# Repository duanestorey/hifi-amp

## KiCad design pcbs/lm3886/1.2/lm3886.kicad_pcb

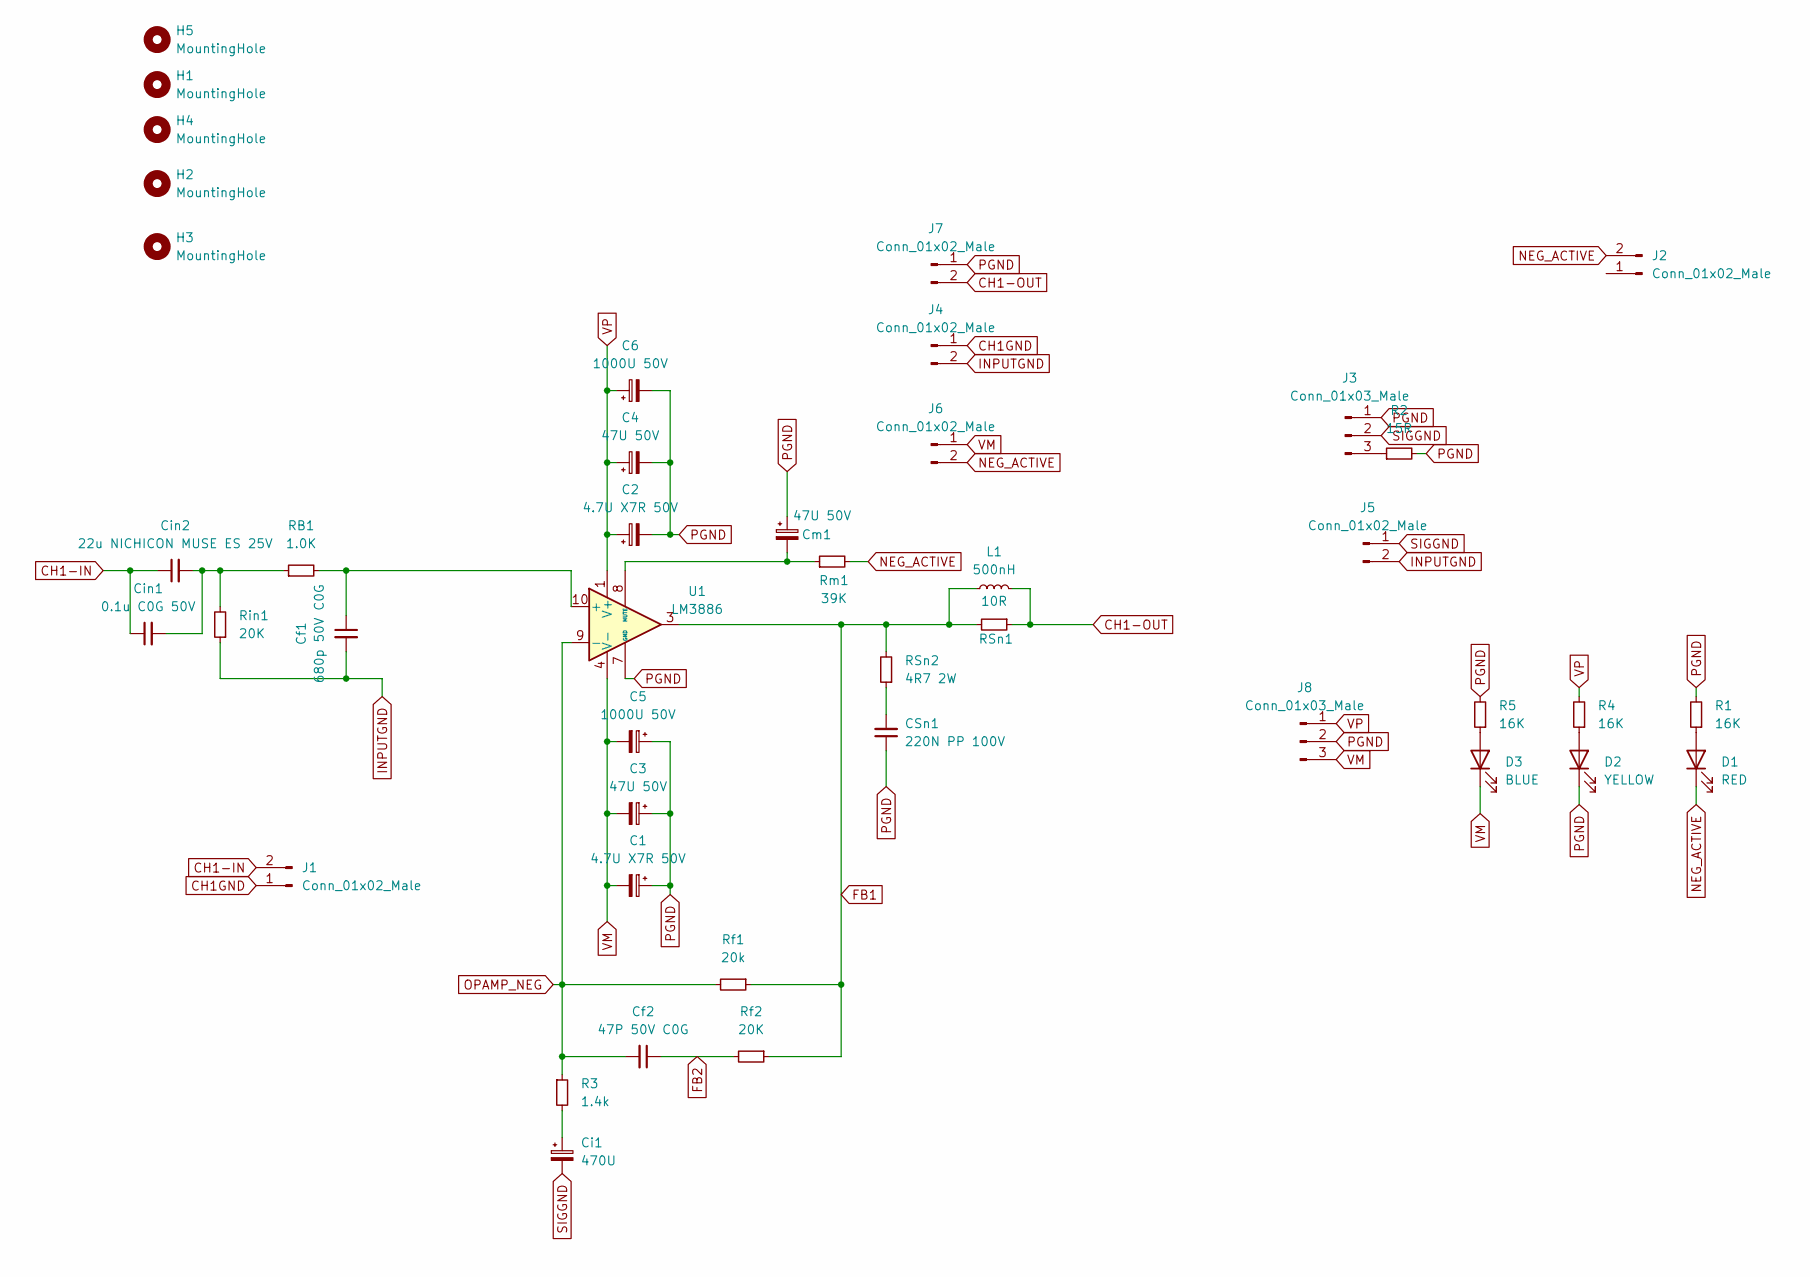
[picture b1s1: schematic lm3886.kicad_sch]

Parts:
C1, C2: 4.7U X7R 50V; C_1206_3216Metric_Pad1.33x1.80mm_HandSolder; Mouser 80-C1206X475J5RACTU
C3, C4: 47U 50V; CP_Radial_D6.3mm_P2.50mm
C5, C6: 1000U 50V; CP_Radial_D12.5mm_P5.00mm
CSn1: 220N PP 100V; C_Rect_L18.0mm_W7.0mm_P15.00mm_FKS3_FKP3; Mouser 505-MKP1D032204D00JB
Cf1: 680p 50V C0G; C_1206_3216Metric_Pad1.33x1.80mm_HandSolder; Mouser 603-CC126GRNPO9BN681
Cf2: 47P 50V C0G; C_1206_3216Metric_Pad1.33x1.80mm_HandSolder; Mouser 791-1206N470F500CT
Ci1: 470U; CP_Radial_D12.5mm_P5.00mm
Cin1: 0.1u C0G 50V; C_1206_3216Metric_Pad1.33x1.80mm_HandSolder; Mouser 81-GRT31C5C1H104FA2L
Cin2: 22u NICHICON MUSE ES 25V; C_Radial_D6.3mm_H5.0mm_P2.50mm
Cm1: 47U 50V; CP_Radial_D6.3mm_P2.50mm
D1: RED; LED_0805_2012Metric_Pad1.15x1.40mm_HandSolder
D2: YELLOW; LED_0805_2012Metric_Pad1.15x1.40mm_HandSolder
D3: BLUE; LED_0805_2012Metric_Pad1.15x1.40mm_HandSolder
H1, H2, H3, H4, H5: MountingHole; M3 Slot
J1, J2: Conn_01x02_Male; JST_PH_B2B-PH-K_1x02_P2.00mm_Vertical
J3: Conn_01x03_Male; PinHeader_1x03_P2.54mm_Vertical
J4, J5, J6: Conn_01x02_Male; PinHeader_1x02_P2.54mm_Vertical
J7: Conn_01x02_Male; JST_VH_B2P-VH_1x02_P3.96mm_Vertical
J8: Conn_01x03_Male; JST_VH_B3P-VH-B_1x03_P3.96mm_Vertical
L1: 500nH; 500nH Inductor Aliexpress Air Gap
R1, R4, R5: 16K; R_0603_1608Metric_Pad0.98x0.95mm_HandSolder
R2: 15R; R_1206_3216Metric_Pad1.30x1.75mm_HandSolder
R3: 1.4k; R_1206_3216Metric_Pad1.30x1.75mm_HandSolder; Mouser 603-RT1206FRE07750RL
RB1: 1.0K; R_1206_3216Metric_Pad1.30x1.75mm_HandSolder; Mouser 603-RT1206FRE131KL
RSn1: 10R; R_4020_10251Metric_Pad1.65x5.30mm_HandSolder; Mouser 279-355010RJT
RSn2: 4R7 2W; R_2512_6332Metric_Pad1.40x3.35mm_HandSolder; Mouser 603-RC2512JK-7W4R7
Rf1: 20k; R_1206_3216Metric_Pad1.30x1.75mm_HandSolder; Mouser 603-RT1206FRD0720KL
Rf2: 20K; R_1206_3216Metric_Pad1.30x1.75mm_HandSolder; Mouser 603-RT1206FRD0720KL
Rin1: 20K; R_1206_3216Metric_Pad1.30x1.75mm_HandSolder; Mouser 603-RT1206FRD0720KL
Rm1: 39K; R_1206_3216Metric_Pad1.30x1.75mm_HandSolder; Mouser 603-RC1206JR-0739KL
U1: LM3886; TO-220-11_P3.4x5.08mm_StaggerOdd_Lead4.85mm_Vertical

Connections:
CH1-IN: Cin1.1, Cin2.1, J1.2
CH1-OUT: J7.2, L1.2, RSn1.1
CH1GND: J1.1, J4.1
FB1: L1.1, RSn1.2, RSn2.2, Rf1.1, Rf2.1, U1.3
FB2: Cf2.1, Rf2.2
INPUTGND: Cf1.2, J4.2, J5.2, Rin1.1
NEG_ACTIVE: D1.1 (K), J2.2, J6.2, Rm1.2
unnamed: CSn1.2, RSn2.1
unnamed: Ci1.1, R3.2
unnamed: Cin1.2, Cin2.2, RB1.1, Rin1.2
unnamed: D1.2 (A), R1.1
unnamed: D2.2 (A), R4.1
unnamed: D3.2 (A), R5.1
unnamed: J3.3, R2.1
unnamed: Cf1.1, RB1.2, U1.10 (+)
unnamed: Cm1.2, Rm1.1, U1.8 (MUTE)
OPAMP_NEG: Cf2.2, R3.1, Rf1.2, U1.9 (-)
PGND: C1.1, C2.2, C3.1, C4.2, C5.1, C6.2, CSn1.1, Cm1.1, D2.1 (K), J3.1, J7.1, J8.2, R1.2, R2.2, R5.2, U1.7 (GND)
SIGGND: Ci1.2, J3.2, J5.1
VM: C1.2, C3.2, C5.2, D3.1 (K), J6.1, J8.3, U1.4 (V-)
VP: C2.1, C4.1, C6.1, J8.1, R4.2, U1.1 (V+), U1.5 (V+)

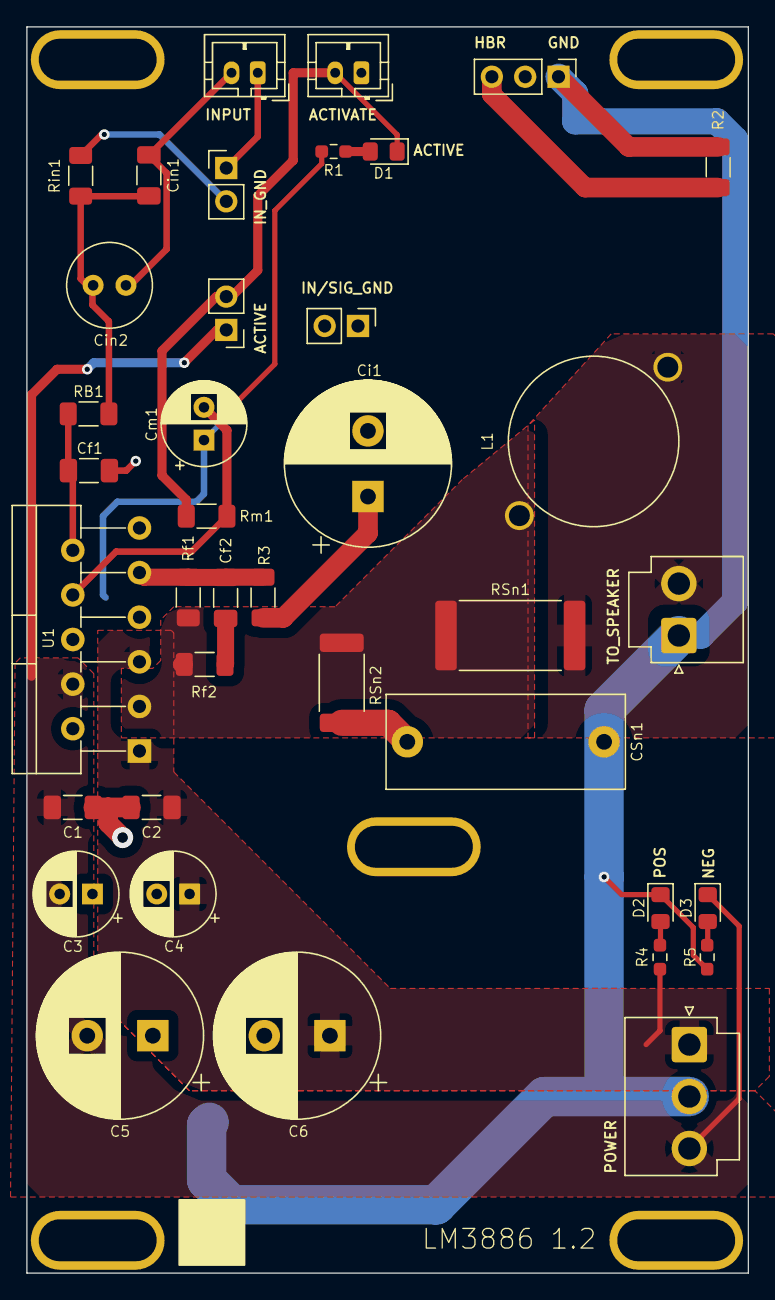
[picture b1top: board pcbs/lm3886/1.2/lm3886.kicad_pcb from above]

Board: 2 copper layers, 55.0 x 95.0 mm, 43 parts (0 on the bottom side), 21 nets.

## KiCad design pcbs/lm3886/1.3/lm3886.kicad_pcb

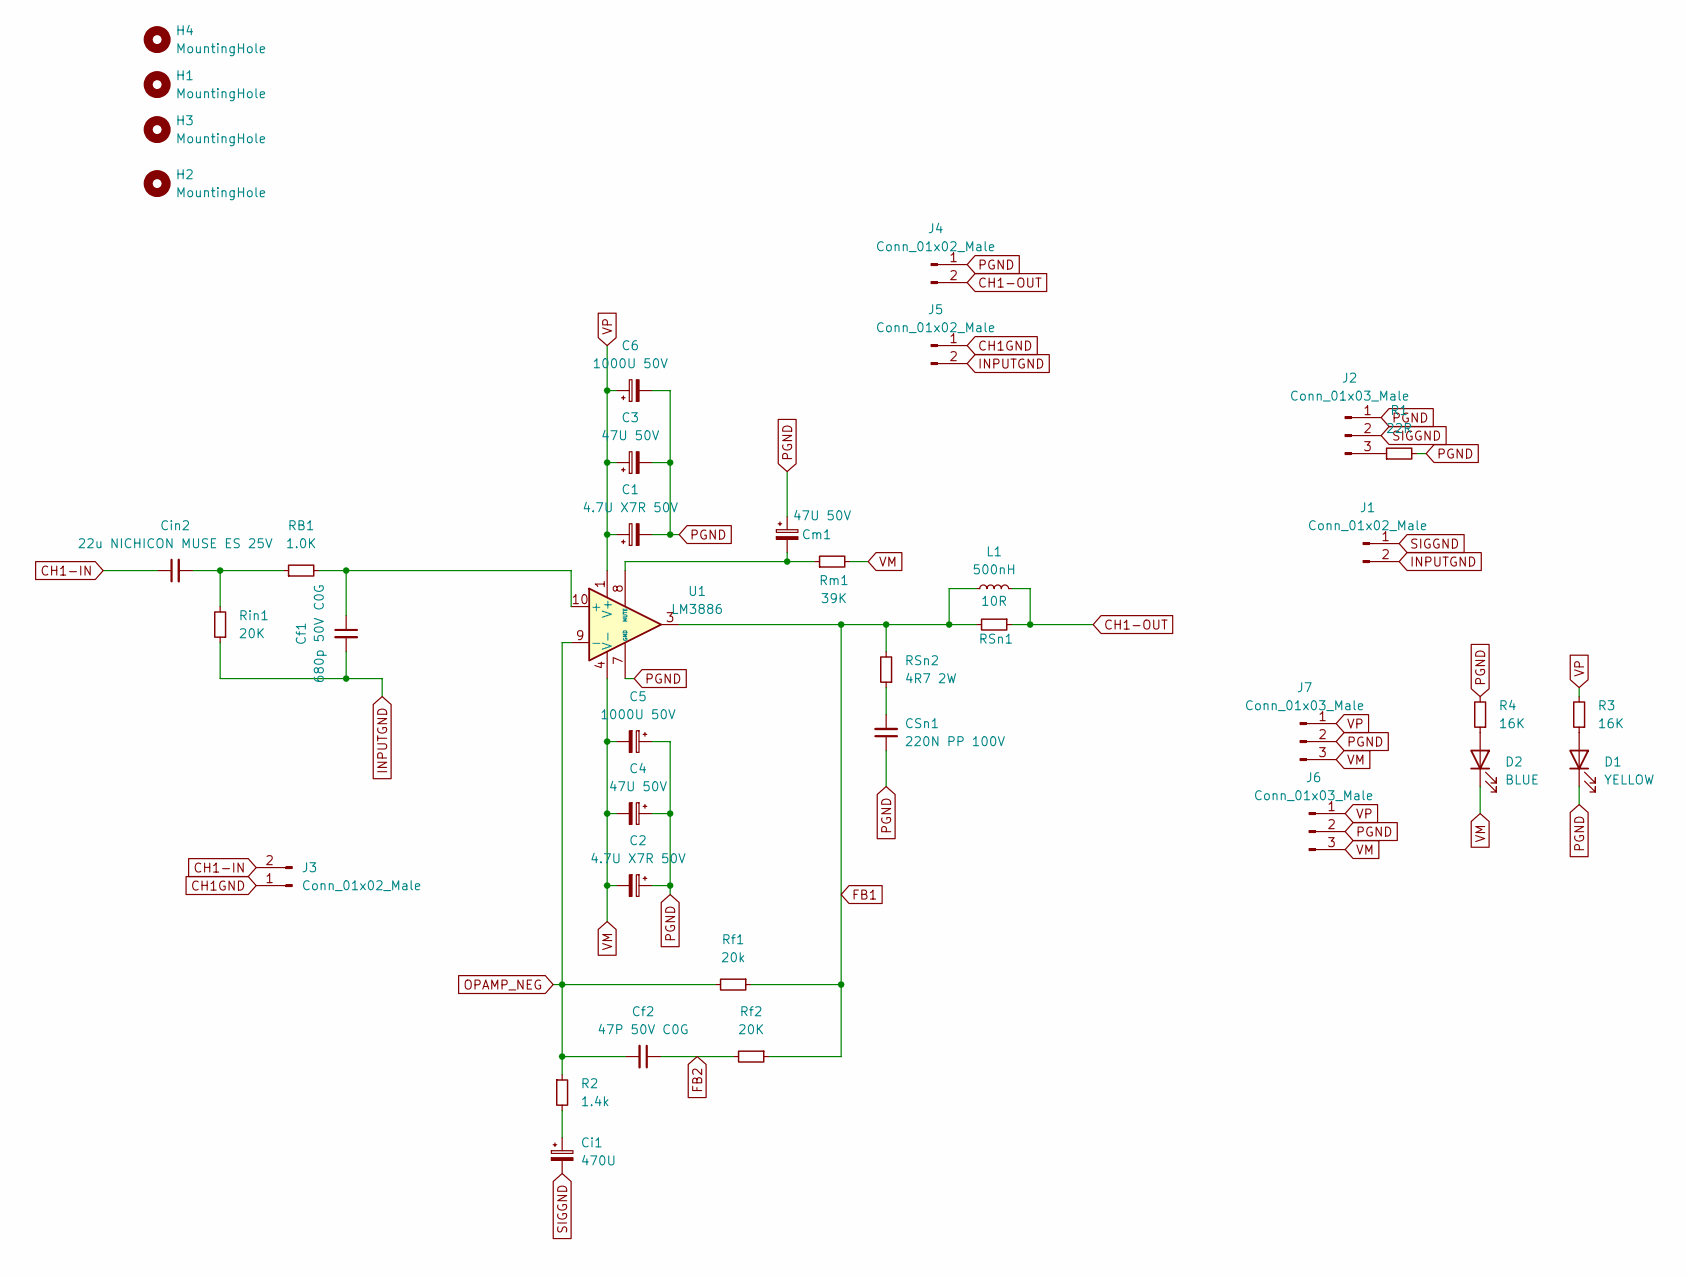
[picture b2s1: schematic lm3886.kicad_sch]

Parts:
C1, C2: 4.7U X7R 50V; C_1206_3216Metric_Pad1.33x1.80mm_HandSolder; Mouser 80-C1206X475J5RACTU
C3, C4: 47U 50V; CP_Radial_D6.3mm_P2.50mm
C5, C6: 1000U 50V; CP_Radial_D12.5mm_P5.00mm
CSn1: 220N PP 100V; C_Rect_L18.0mm_W7.0mm_P15.00mm_FKS3_FKP3; Mouser 505-MKP1D032204D00JB
Cf1: 680p 50V C0G; C_1206_3216Metric_Pad1.33x1.80mm_HandSolder; Mouser 603-CC126GRNPO9BN681
Cf2: 47P 50V C0G; C_1206_3216Metric_Pad1.33x1.80mm_HandSolder; Mouser 791-1206N470F500CT
Ci1: 470U; CP_Radial_D12.5mm_P5.00mm
Cin2: 22u NICHICON MUSE ES 25V; C_Radial_D6.3mm_H5.0mm_P2.50mm
Cm1: 47U 50V; CP_Radial_D6.3mm_P2.50mm
D1: YELLOW; LED_0805_2012Metric_Pad1.15x1.40mm_HandSolder
D2: BLUE; LED_0805_2012Metric_Pad1.15x1.40mm_HandSolder
H1, H2, H3, H4: MountingHole; MountingHole_3.2mm_M3_DIN965_Pad_TopOnly
J1, J5: Conn_01x02_Male; PinHeader_1x02_P2.54mm_Vertical
J2: Conn_01x03_Male; PinHeader_1x03_P2.54mm_Vertical
J3: Conn_01x02_Male; JST_PH_B2B-PH-K_1x02_P2.00mm_Vertical
J4: Conn_01x02_Male; JST_VH_B2P-VH_1x02_P3.96mm_Vertical
J6, J7: Conn_01x03_Male; JST_VH_B3P-VH-B_1x03_P3.96mm_Vertical
L1: 500nH; 500nH Inductor Aliexpress Air Gap
R1: 22R; R_1206_3216Metric_Pad1.30x1.75mm_HandSolder
R2: 1.4k; R_1206_3216Metric_Pad1.30x1.75mm_HandSolder; Mouser 603-RT1206FRE07750RL
R3, R4: 16K; R_0603_1608Metric_Pad0.98x0.95mm_HandSolder
RB1: 1.0K; R_1206_3216Metric_Pad1.30x1.75mm_HandSolder; Mouser 603-RT1206FRE131KL
RSn1: 10R; R_4020_10251Metric_Pad1.65x5.30mm_HandSolder; Mouser 279-355010RJT
RSn2: 4R7 2W; R_2512_6332Metric_Pad1.40x3.35mm_HandSolder; Mouser 603-RC2512JK-7W4R7
Rf1: 20k; R_1206_3216Metric_Pad1.30x1.75mm_HandSolder; Mouser 603-RT1206FRD0720KL
Rf2: 20K; R_1206_3216Metric_Pad1.30x1.75mm_HandSolder; Mouser 603-RT1206FRD0720KL
Rin1: 20K; R_1206_3216Metric_Pad1.30x1.75mm_HandSolder; Mouser 603-RT1206FRD0720KL
Rm1: 39K; R_1206_3216Metric_Pad1.30x1.75mm_HandSolder; Mouser 603-RC1206JR-0739KL
U1: LM3886; TO-220-11_P3.4x5.08mm_StaggerOdd_Lead4.85mm_Vertical

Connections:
CH1-IN: Cin2.1, J3.2; also elsewhere on the board
CH1-OUT: J4.2, L1.2, RSn1.1
CH1GND: J3.1, J5.1
FB1: L1.1, RSn1.2, RSn2.2, Rf1.1, Rf2.1, U1.3
FB2: Cf2.1, Rf2.2
INPUTGND: Cf1.2, J1.2, J5.2, Rin1.1
unnamed: CSn1.2, RSn2.1
unnamed: Ci1.1, R2.2
unnamed 8: Cin2.2, RB1.1, Rin1.2; also elsewhere on the board
unnamed: D1.2 (A), R3.1
unnamed: D2.2 (A), R4.1
unnamed: J2.3, R1.1
unnamed: Cf1.1, RB1.2, U1.10 (+)
unnamed: Cm1.2, Rm1.1, U1.8 (MUTE)
OPAMP_NEG: Cf2.2, R2.1, Rf1.2, U1.9 (-)
PGND: C1.2, C2.1, C3.2, C4.1, C5.1, C6.2, CSn1.1, Cm1.1, D1.1 (K), J2.1, J4.1, J6.2, J7.2, R1.2, R4.2, U1.7 (GND)
SIGGND: Ci1.2, J1.1, J2.2
VM: C2.2, C4.2, C5.2, D2.1 (K), J6.3, J7.3, Rm1.2, U1.4 (V-)
VP: C1.1, C3.1, C6.1, J6.1, J7.1, R3.2, U1.1 (V+), U1.5 (V+)

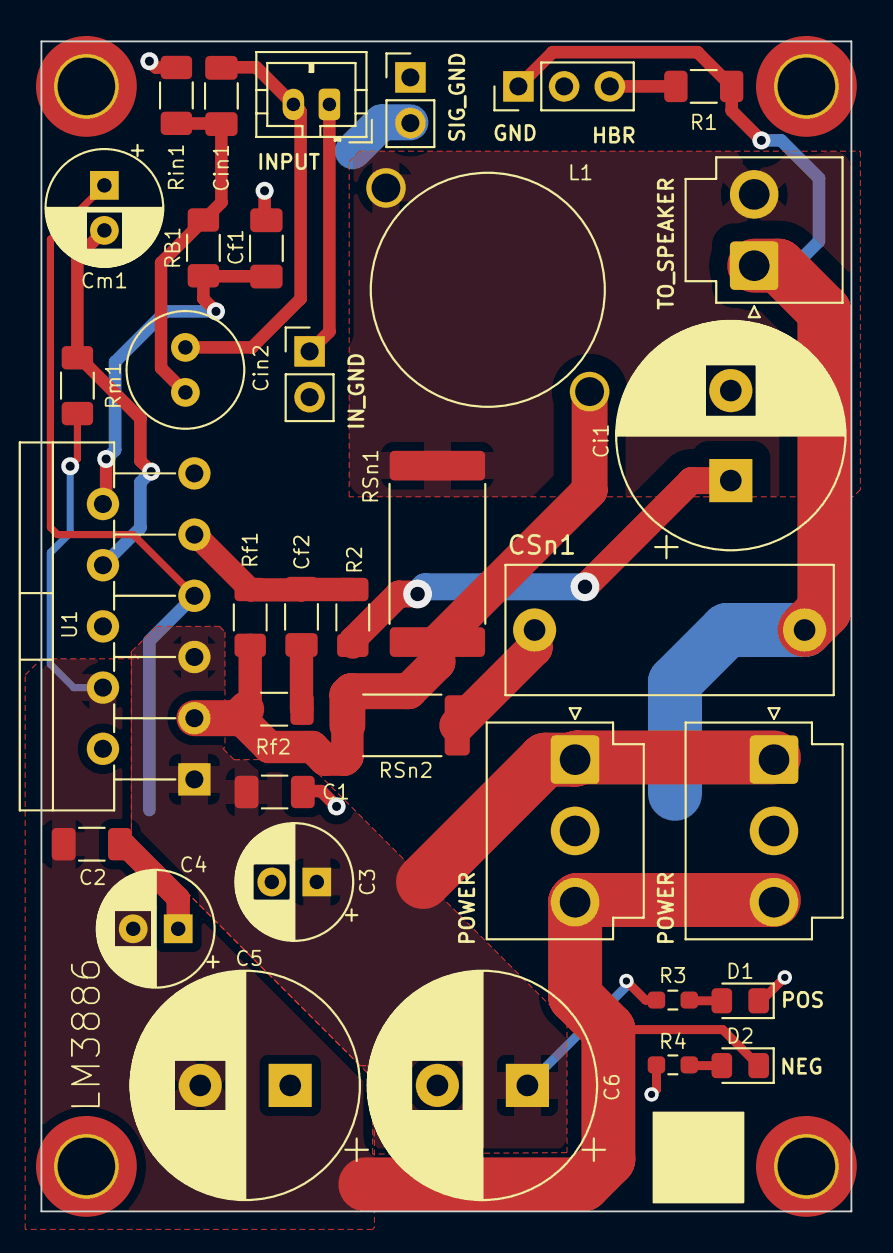
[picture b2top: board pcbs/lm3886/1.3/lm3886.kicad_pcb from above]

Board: 2 copper layers, 45.0 x 65.0 mm, 39 parts (0 on the bottom side), 19 nets.

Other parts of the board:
Cin1: 0.1u C0G 50V; C_1206_3216Metric_Pad1.33x1.80mm_HandSolder

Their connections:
CH1-IN: Cin1.1; also elsewhere on the board
unnamed 8: Cin1.2; also elsewhere on the board

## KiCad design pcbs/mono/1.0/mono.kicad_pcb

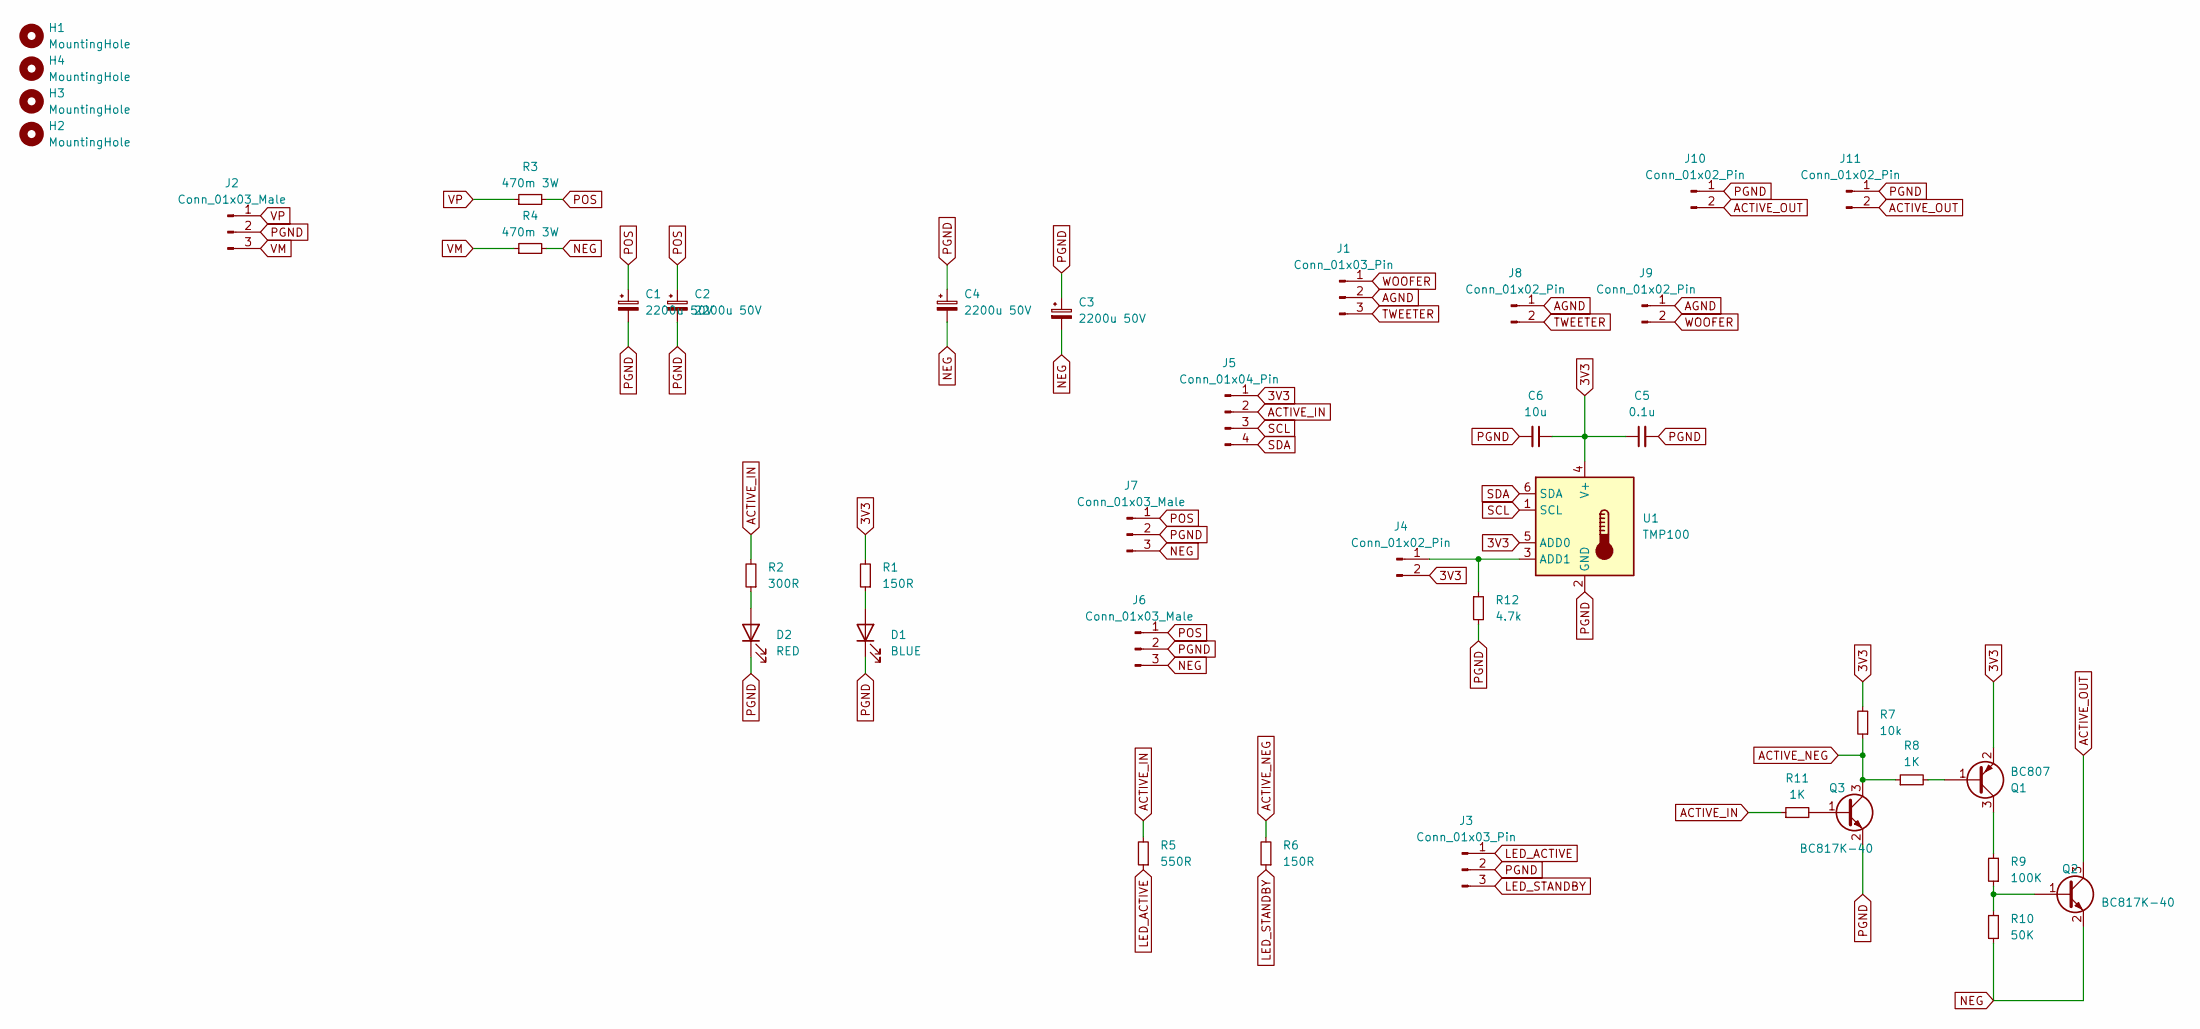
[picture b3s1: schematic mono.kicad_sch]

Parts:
C1, C2, C3, C4: 2200u 50V; CP_Radial_D16.0mm_P7.50mm; Mouser 80-ESH228M050AM3AA
C5: 0.1u; C_0805_2012Metric_Pad1.18x1.45mm_HandSolder
C6: 10u; C_1206_3216Metric_Pad1.33x1.80mm_HandSolder
D1: BLUE; LED_0603_1608Metric_Pad1.05x0.95mm_HandSolder
D2: RED; LED_0603_1608Metric_Pad1.05x0.95mm_HandSolder
H1, H2, H3, H4: MountingHole; MountingHole_3.2mm_M3_DIN965_Pad_TopOnly
J1, J3: Conn_01x03_Pin; JST_PH_B3B-PH-K_1x03_P2.00mm_Vertical
J2, J6, J7: Conn_01x03_Male; JST_VH_B3P-VH-B_1x03_P3.96mm_Vertical
J4: Conn_01x02_Pin; PinHeader_1x02_P2.54mm_Vertical
J5: Conn_01x04_Pin; JST_PH_B4B-PH-K_1x04_P2.00mm_Vertical
J8, J9, J10, J11: Conn_01x02_Pin; JST_PH_B2B-PH-K_1x02_P2.00mm_Vertical
Q1: BC807; TSOT-23; Mouser 637-BC807-16
Q2, Q3: BC817K-40; TSOT-23; Mouser 637-BC817K-40
R1, R6: 150R; R_0603_1608Metric_Pad0.98x0.95mm_HandSolder
R2: 300R; R_0603_1608Metric_Pad0.98x0.95mm_HandSolder
R3, R4: 470m 3W; R_1218_3246Metric_Pad1.22x4.75mm_HandSolder; Mouser RLW73PA3FR47TDF
R5: 550R; R_0603_1608Metric_Pad0.98x0.95mm_HandSolder
R7: 10k; R_0603_1608Metric_Pad0.98x0.95mm_HandSolder
R8, R11: 1K; R_0603_1608Metric_Pad0.98x0.95mm_HandSolder
R9: 100K; R_0603_1608Metric_Pad0.98x0.95mm_HandSolder
R10: 50K; R_0603_1608Metric_Pad0.98x0.95mm_HandSolder
R12: 4.7k; R_0603_1608Metric_Pad0.98x0.95mm_HandSolder
U1: TMP100; SOT-23-6

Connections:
3V3: C5.1, C6.1, J4.2, J5.1, Q1.2 (E), R1.2, R7.2, U1.4 (V+), U1.5 (ADD0)
ACTIVE_IN: J5.2, R2.2, R5.2, R11.1
ACTIVE_NEG: Q3.3 (C), R6.2, R7.1, R8.1
ACTIVE_OUT: J10.2, J11.2, Q2.3 (C)
AGND: J1.2, J8.1, J9.1
LED_ACTIVE: J3.1, R5.1
LED_STANDBY: J3.3, R6.1
NEG: C3.2, C4.2, J6.3, J7.3, Q2.2 (E), R4.2, R10.1
unnamed: D1.2 (A), R1.1
unnamed: D2.2 (A), R2.1
unnamed: J4.1, R12.1, U1.3 (ADD1)
unnamed: Q1.1 (B), R8.2
unnamed: Q1.3 (C), R9.2
unnamed: Q2.1 (B), R9.1, R10.2
unnamed: Q3.1 (B), R11.2
PGND: C1.2, C2.2, C3.1, C4.1, C5.2, C6.2, D1.1 (K), D2.1 (K), J2.2, J3.2, J6.2, J7.2, J10.1, J11.1, Q3.2 (E), R12.2, U1.2 (GND)
POS: C1.1, C2.1, J6.1, J7.1, R3.2
SCL: J5.3, U1.1 (SCL)
SDA: J5.4, U1.6 (SDA)
TWEETER: J1.3, J8.2
VM: J2.3, R4.1
VP: J2.1, R3.1
WOOFER: J1.1, J9.2

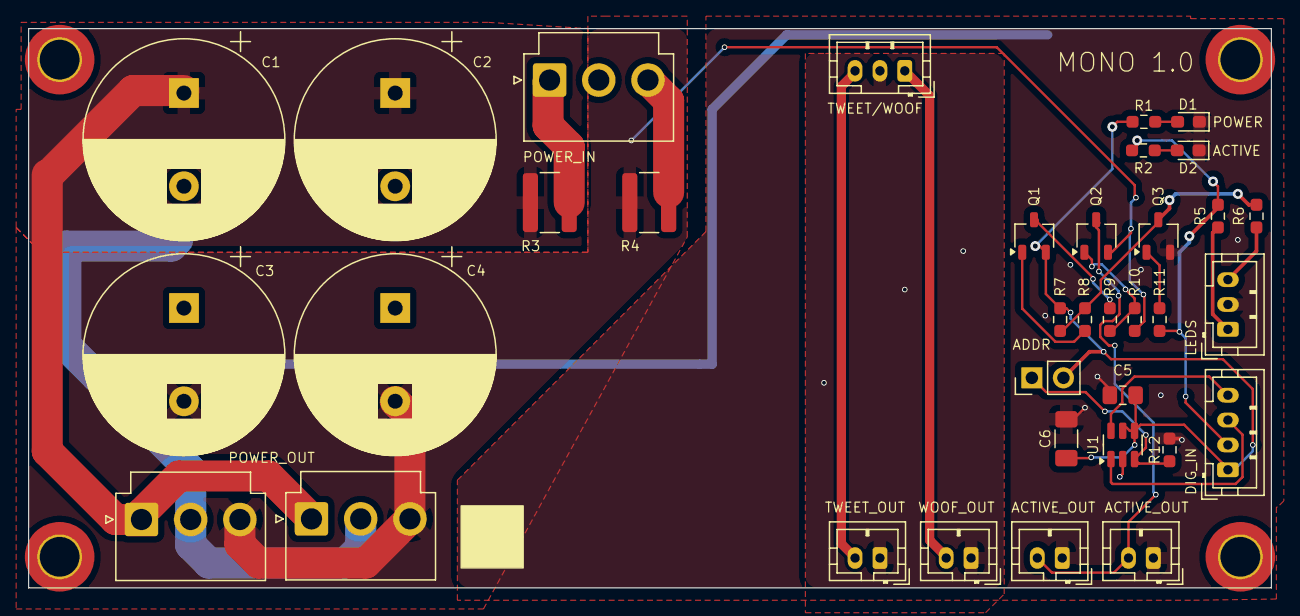
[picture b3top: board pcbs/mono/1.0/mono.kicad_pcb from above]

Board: 2 copper layers, 100.0 x 45.0 mm, 39 parts (0 on the bottom side), 23 nets.

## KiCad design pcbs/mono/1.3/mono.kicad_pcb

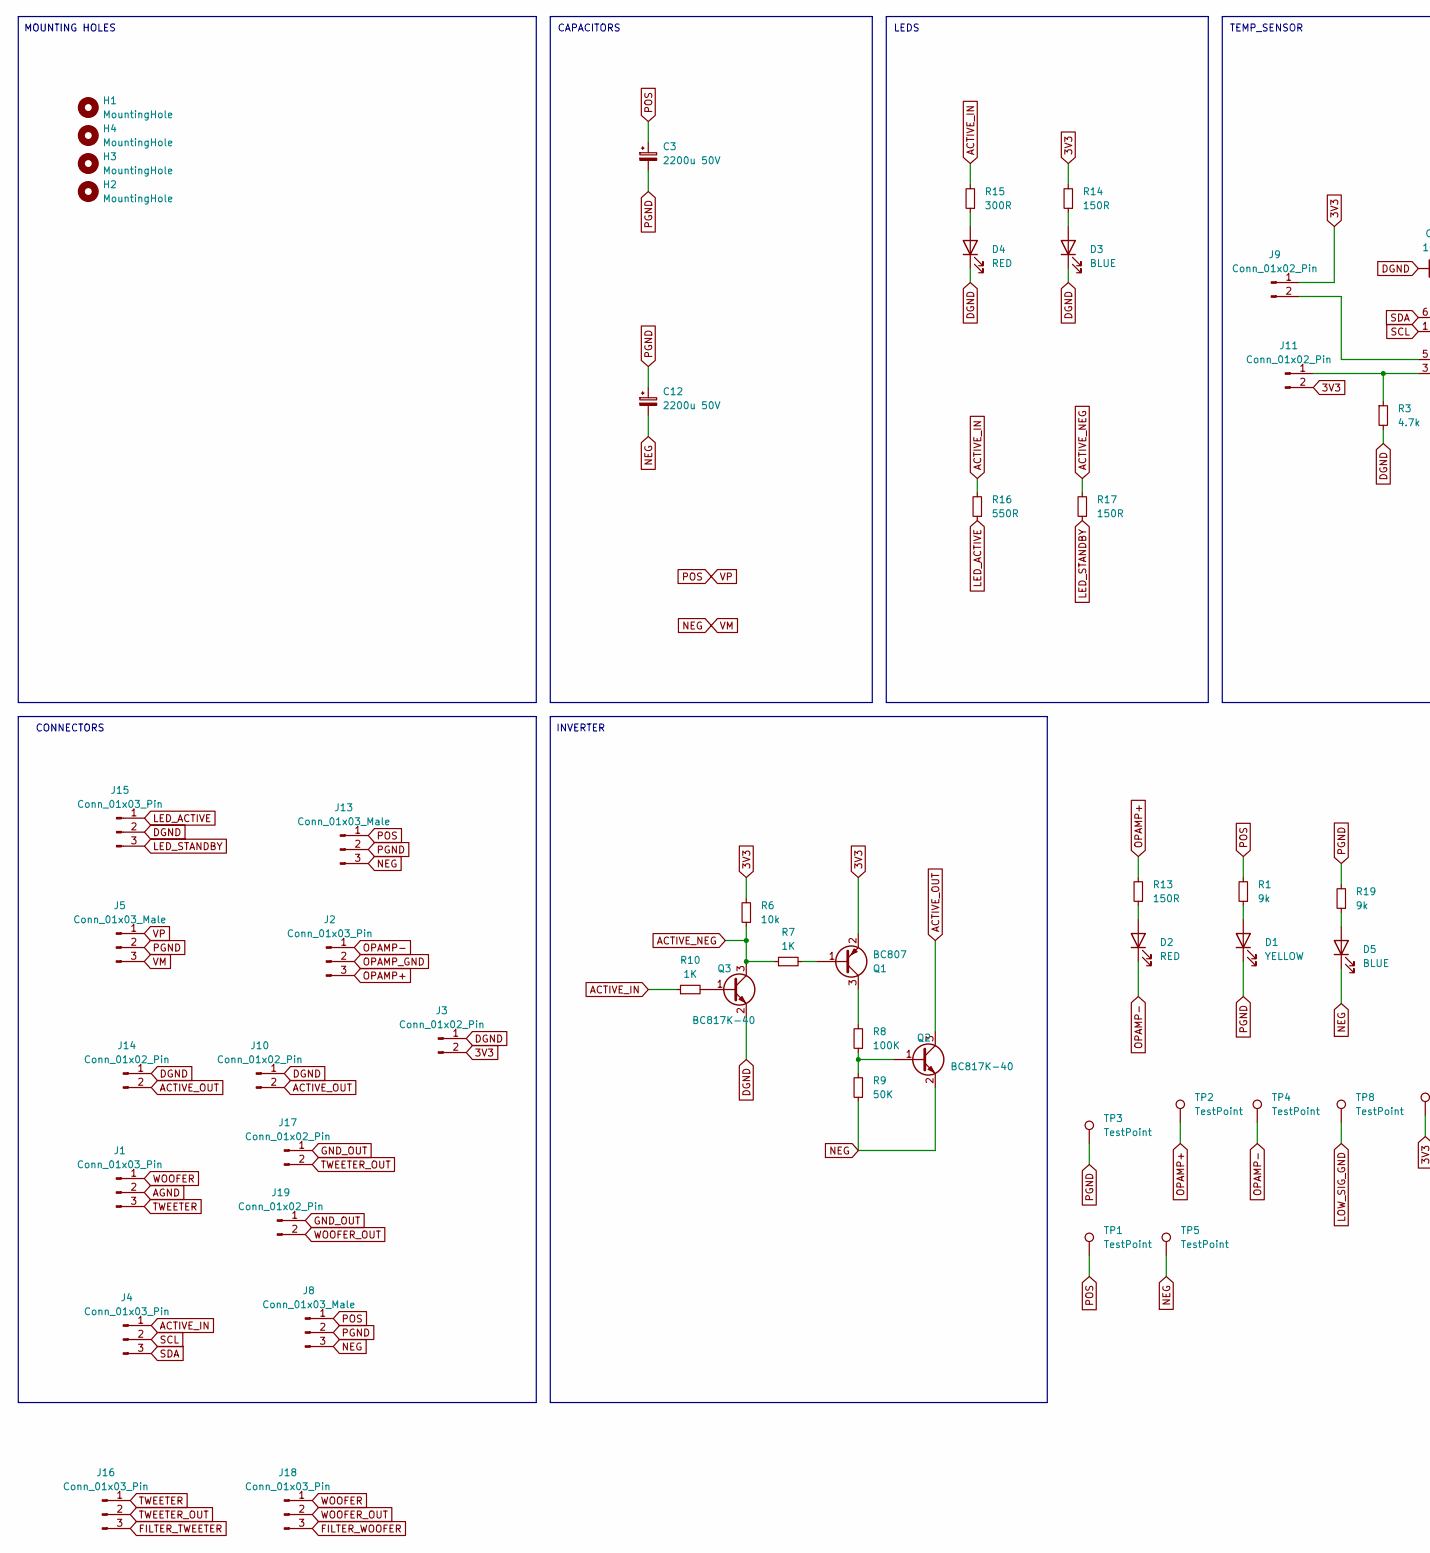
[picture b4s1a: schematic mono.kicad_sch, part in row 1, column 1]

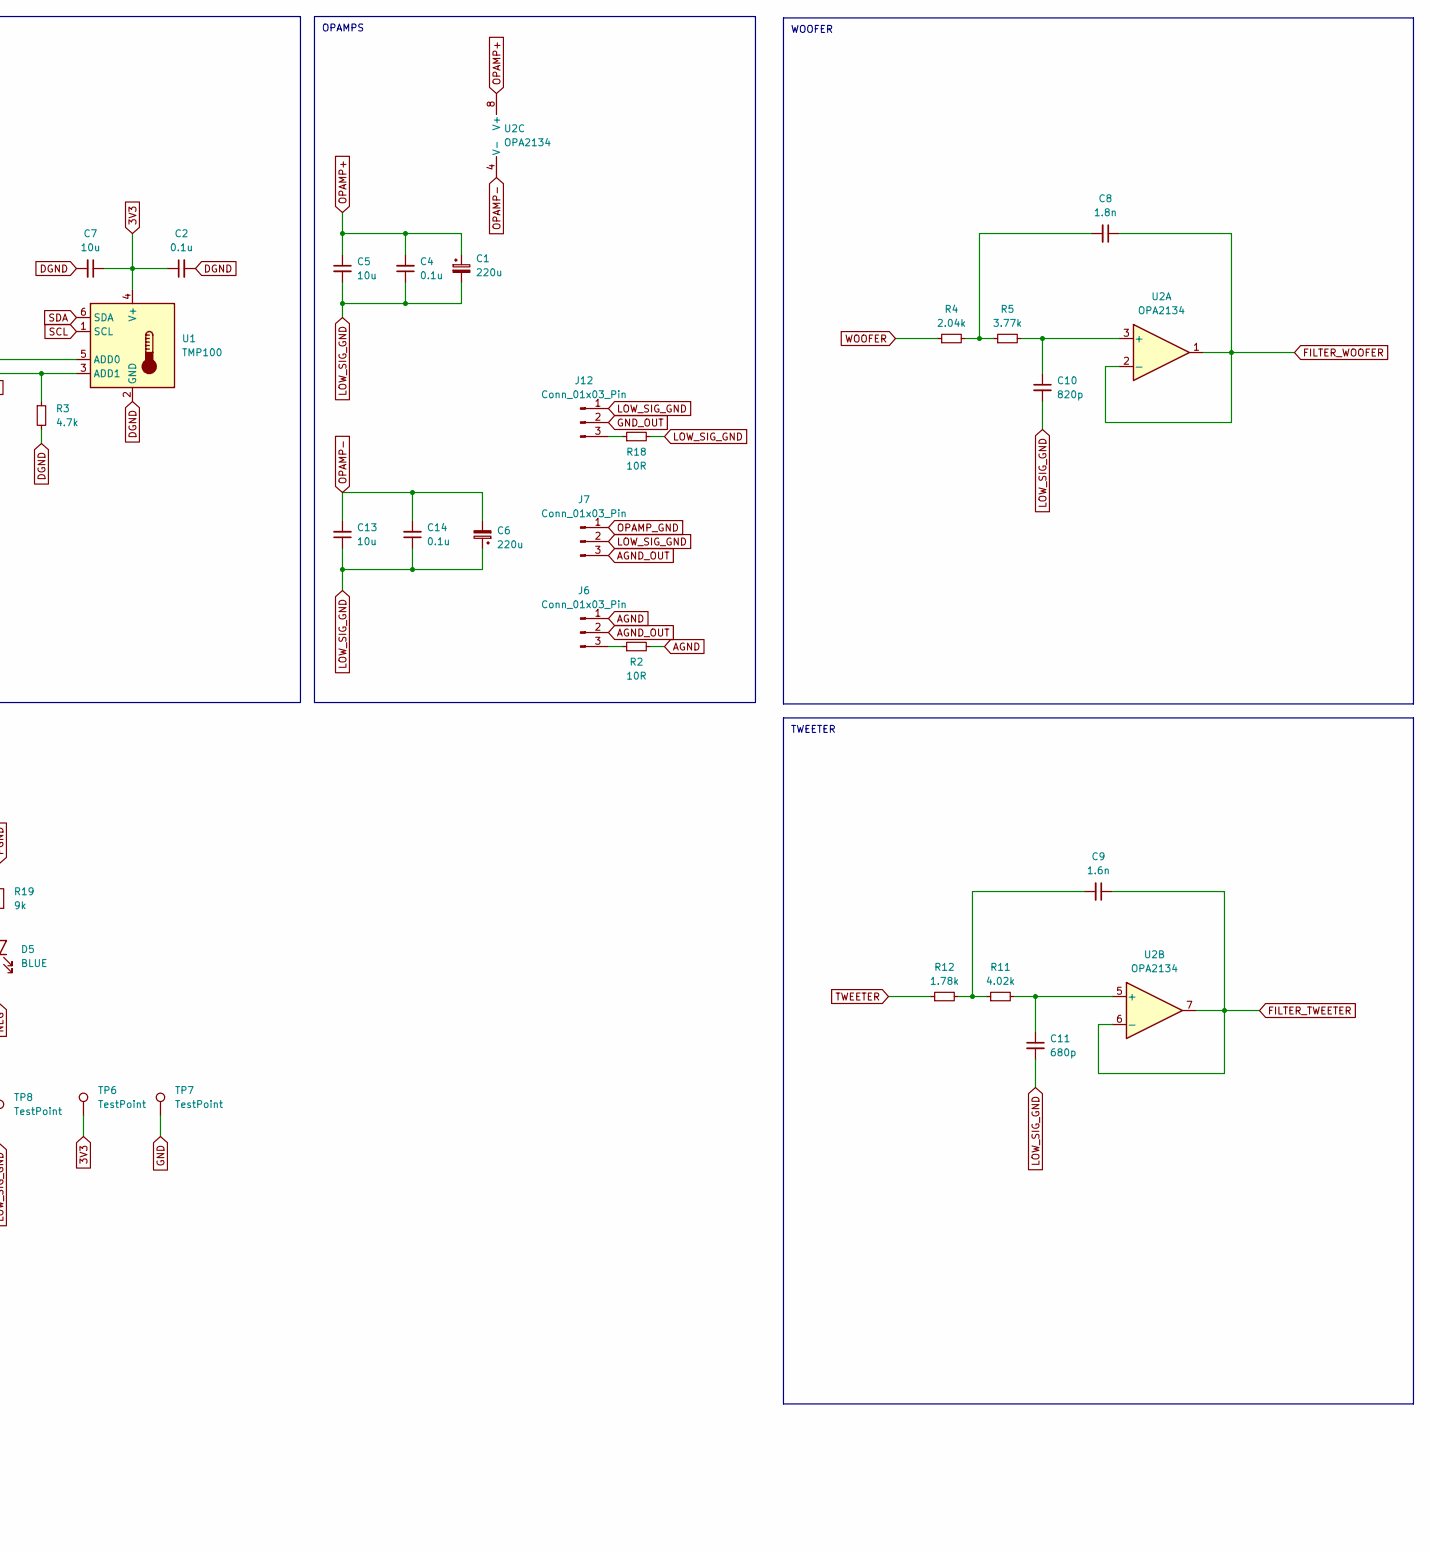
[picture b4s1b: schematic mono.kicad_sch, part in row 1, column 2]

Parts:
C1, C6: 220u; CP_Radial_D6.3mm_P2.50mm
C2, C4, C14: 0.1u; C_0805_2012Metric_Pad1.18x1.45mm_HandSolder
C3, C12: 2200u 50V; CP_Radial_D16.0mm_P7.50mm; Mouser 80-ESH228M050AM3AA
C5, C7, C13: 10u; C_1206_3216Metric_Pad1.33x1.80mm_HandSolder
C8: 1.8n; C_0805_2012Metric_Pad1.18x1.45mm_HandSolder
C9: 1.6n; C_0805_2012Metric_Pad1.18x1.45mm_HandSolder; Mouser 81-GCM2165C2A162FA6D
C10: 820p; C_0805_2012Metric_Pad1.18x1.45mm_HandSolder
C11: 680p; C_0805_2012Metric_Pad1.18x1.45mm_HandSolder; Mouser 603-CC805GRNPO9BN681
D1: YELLOW; LED_0805_2012Metric_Pad1.15x1.40mm_HandSolder
D2, D4: RED; LED_0805_2012Metric_Pad1.15x1.40mm_HandSolder
D3, D5: BLUE; LED_0805_2012Metric_Pad1.15x1.40mm_HandSolder
H1, H2, H3, H4: MountingHole; MountingHole_3.2mm_M3_DIN965_Pad_TopOnly
J1, J2, J4, J15: Conn_01x03_Pin; JST_PH_B3B-PH-K_1x03_P2.00mm_Vertical
J3, J10, J14, J17, J19: Conn_01x02_Pin; JST_PH_B2B-PH-K_1x02_P2.00mm_Vertical
J5, J8, J13: Conn_01x03_Male; JST_VH_B3P-VH-B_1x03_P3.96mm_Vertical
J6, J7, J12, J16, J18: Conn_01x03_Pin; PinHeader_1x03_P2.54mm_Vertical
J9, J11: Conn_01x02_Pin; PinHeader_1x02_P2.54mm_Vertical
Q1: BC807; TSOT-23; Mouser 637-BC807-16
Q2, Q3: BC817K-40; TSOT-23; Mouser 637-BC817K-40
R1, R19: 9k; R_0603_1608Metric_Pad0.98x0.95mm_HandSolder
R2, R18: 10R; R_0805_2012Metric_Pad1.20x1.40mm_HandSolder
R3: 4.7k; R_0603_1608Metric_Pad0.98x0.95mm_HandSolder
R4: 2.04k; R_0805_2012Metric_Pad1.20x1.40mm_HandSolder
R5: 3.77k; R_0805_2012Metric_Pad1.20x1.40mm_HandSolder
R6: 10k; R_0805_2012Metric_Pad1.20x1.40mm_HandSolder
R7, R10: 1K; R_0805_2012Metric_Pad1.20x1.40mm_HandSolder
R8: 100K; R_0805_2012Metric_Pad1.20x1.40mm_HandSolder
R9: 50K; R_0805_2012Metric_Pad1.20x1.40mm_HandSolder
R11: 4.02k; R_0805_2012Metric_Pad1.20x1.40mm_HandSolder; Mouser 754-RG2012P-4021-BT5
R12: 1.78k; R_0805_2012Metric_Pad1.20x1.40mm_HandSolder; Mouser 667-ERA-6AEB1781V
R13, R14, R17: 150R; R_0603_1608Metric_Pad0.98x0.95mm_HandSolder
R15: 300R; R_0603_1608Metric_Pad0.98x0.95mm_HandSolder
R16: 550R; R_0603_1608Metric_Pad0.98x0.95mm_HandSolder
TP1, TP2, TP3, TP4, TP5, TP6, TP7, TP8: TestPoint; TestPoint_THTPad_2.5x2.5mm_Drill1.2mm
U1: TMP100; SOT-23-6
U2: OPA2134; DIP-8_W7.62mm

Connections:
3V3: C2.1, C7.1, J3.2, J9.1, J11.2, Q1.2 (E), R6.2, R14.2, TP6.1, U1.4 (V+)
ACTIVE_IN: J4.1, R10.1, R15.2, R16.2
ACTIVE_NEG: Q3.3 (C), R6.1, R7.1, R17.2
ACTIVE_OUT: J10.2, J14.2, Q2.3 (C)
AGND: J1.2, J6.1, R2.2
AGND_OUT: J6.2, J7.3
DGND: C2.2, C7.2, D3.1 (K), D4.1 (K), J3.1, J10.1, J14.1, J15.2, Q3.2 (E), R3.2, U1.2 (GND)
FILTER_TWEETER: C9.1, J16.3, U2.6 (-), U2.7
FILTER_WOOFER: C8.1, J18.3, U2.1, U2.2 (-)
GND: TP7.1
GND_OUT: J12.2, J17.1, J19.1
LED_ACTIVE: J15.1, R16.1
LED_STANDBY: J15.3, R17.1
LOW_SIG_GND: C1.2, C4.1, C5.2, C6.1, C10.2, C11.2, C13.1, C14.1, J7.2, J12.1, R18.2, TP8.1
NEG: C12.2, D5.1 (K), J5.3, J8.3, J13.3, Q2.2 (E), R9.1, TP5.1
unnamed: C8.2, R4.2, R5.1
unnamed: C9.2, R11.1, R12.2
unnamed: D1.2 (A), R1.1
unnamed: D2.2 (A), R13.1
unnamed: D3.2 (A), R14.1
unnamed: D4.2 (A), R15.1
unnamed: D5.2 (A), R19.1
unnamed: J6.3, R2.1
unnamed: J9.2, U1.5 (ADD0)
unnamed: J11.1, R3.1, U1.3 (ADD1)
unnamed: J12.3, R18.1
unnamed: Q1.1 (B), R7.2
unnamed: Q1.3 (C), R8.2
unnamed: Q2.1 (B), R8.1, R9.2
unnamed: Q3.1 (B), R10.2
unnamed: C10.1, R5.2, U2.3 (+)
unnamed: C11.1, R11.2, U2.5 (+)
OPAMP+: C1.1, C4.2, C5.1, J2.3, R13.2, TP2.1, U2.8 (V+)
OPAMP-: C6.2, C13.2, C14.2, D2.1 (K), J2.1, TP4.1, U2.4 (V-)
OPAMP_GND: J2.2, J7.1
PGND: C3.2, C12.1, D1.1 (K), J5.2, J8.2, J13.2, R19.2, TP3.1
POS: C3.1, J5.1, J8.1, J13.1, R1.2, TP1.1
SCL: J4.2, U1.1 (SCL)
SDA: J4.3, U1.6 (SDA)
TWEETER: J1.3, J16.1, R12.1
TWEETER_OUT: J16.2, J17.2
WOOFER: J1.1, J18.1, R4.1
WOOFER_OUT: J18.2, J19.2

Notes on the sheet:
INVERTER
TWEETER
CAPACITORS
WOOFER
MOUNTING HOLES
LEDS
CONNECTORS
TEMP_SENSOR
OPAMPS

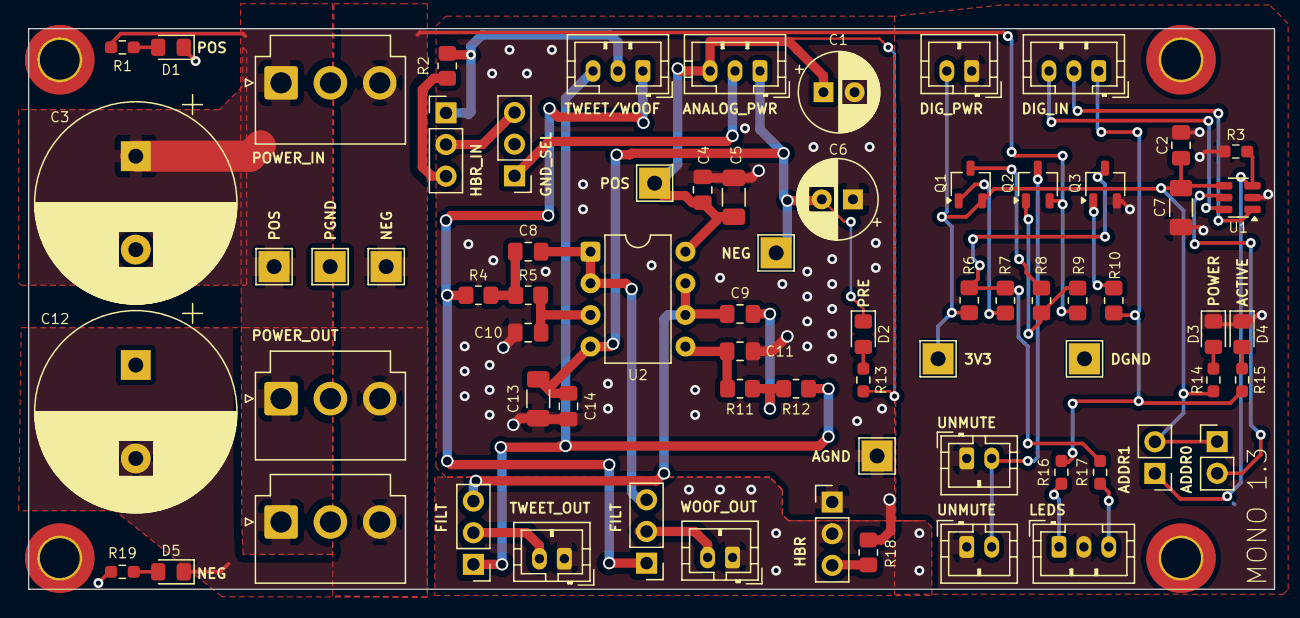
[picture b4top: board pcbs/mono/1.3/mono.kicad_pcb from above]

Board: 2 copper layers, 100.0 x 45.0 mm, 74 parts (0 on the bottom side), 42 nets.
